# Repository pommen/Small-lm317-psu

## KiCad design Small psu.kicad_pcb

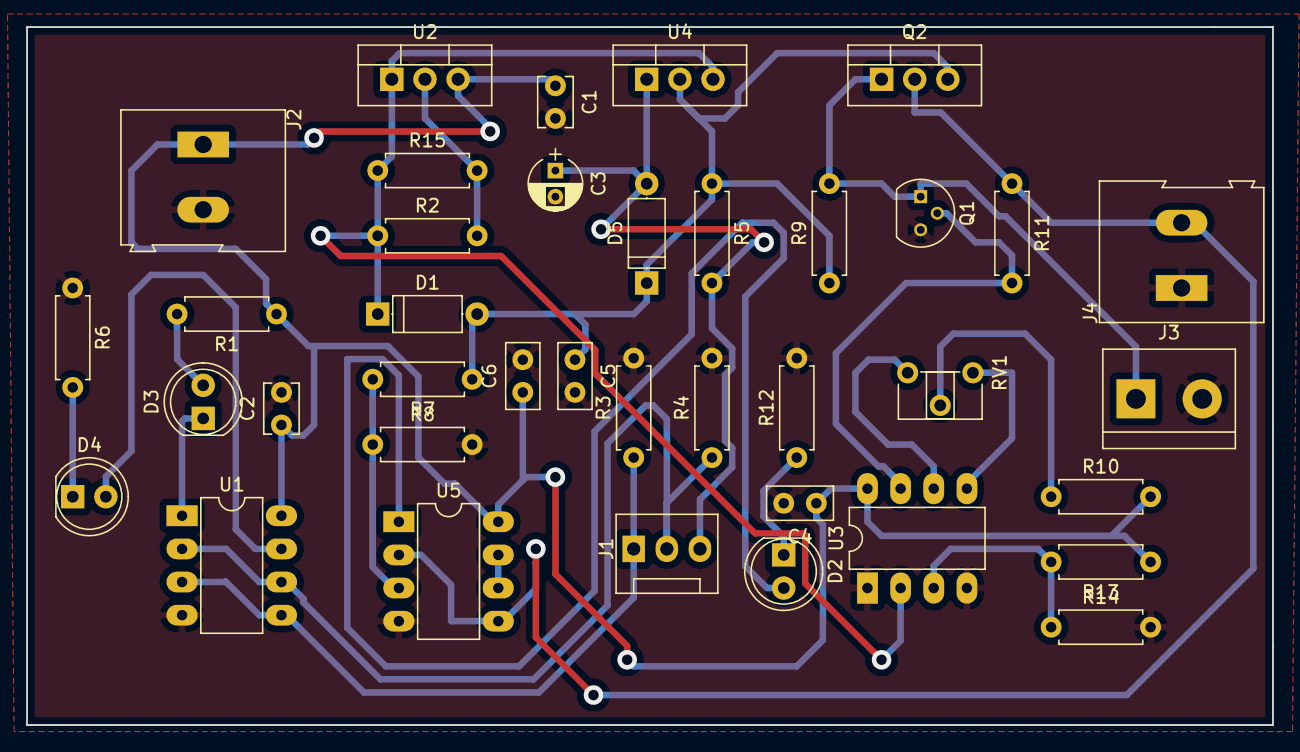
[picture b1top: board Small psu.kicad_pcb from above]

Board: 2 copper layers, 95.5 x 53.5 mm, 38 parts (0 on the bottom side), 23 nets.

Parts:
C1, C2: 0.1u; C_Disc_D3.8mm_W2.6mm_P2.50mm
C3: 10u; CP_Radial_D4.0mm_P2.00mm
C4, C6: 0.1u; C_Disc_D5.0mm_W2.5mm_P2.50mm
C5: 1u; C_Disc_D5.0mm_W2.5mm_P2.50mm
D1, D5: 1n4002; D_A-405_P7.62mm_Horizontal
D2: CC LED; LED_D5.0mm
D3: 5v LED; LED_D5.0mm
D4: 3v LED; LED_D5.0mm
J1: V select sw; Fan_Pin_Header_Straight_1x03
J2: VDC-in; AK300-2
J3: reset sw; bornier2
J4: V out; AK300-2
Q1: BC547; TO-92_Molded_Narrow
Q2: FQP27P06; TO-220_Vertical
R1, R3, R6: 1k6; R_Axial_DIN0207_L6.3mm_D2.5mm_P7.62mm_Horizontal
R2, R15: R; R_Axial_DIN0207_L6.3mm_D2.5mm_P7.62mm_Horizontal
R4: 3k; R_Axial_DIN0207_L6.3mm_D2.5mm_P7.62mm_Horizontal
R5, R14: 1k; R_Axial_DIN0207_L6.3mm_D2.5mm_P7.62mm_Horizontal
R7, R8, R12, R13: 4k7; R_Axial_DIN0207_L6.3mm_D2.5mm_P7.62mm_Horizontal
R9, R11: 100k; R_Axial_DIN0207_L6.3mm_D2.5mm_P7.62mm_Horizontal
R10: 5k6; R_Axial_DIN0207_L6.3mm_D2.5mm_P7.62mm_Horizontal
RV1: 5k; Potentiometer_Trimmer_ACP_CA6h_Vertical
U1, U5: LM358; DIP-8_W7.62mm_LongPads
U2, U4: LM317T; TO-220_Vertical
U3: LM311N; DIP-8_W7.62mm_LongPads

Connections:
3v3LED: J1.1, R3.1, U1.3, U1.5
5vLED: J1.2, R4.1, U1.2, U1.6
GND: C1.2, C2.2, C3.2, C4.2, C5.2, C6.2, J2.2, J3.2, J4.1, Q1.3, R3.2, R4.2, R6.1, R8.2, R12.2, R14.2, U1.4, U3.1, U3.4, U5.4
unnamed: C3.1, D5.2, J1.3, R5.2, U4.1
unnamed: C5.1, D1.2, D5.1, Q2.3, R5.1, R7.1, R9.1, U4.2
unnamed: D2.1, R12.1
unnamed: D2.2, U5.1
unnamed: D3.1, U1.1
unnamed: D3.2, R1.2
unnamed: D4.1, R6.2
unnamed: D4.2, U1.7
unnamed: J3.1, Q1.1, Q2.1, R9.2
unnamed: J4.2, Q2.2, R11.1, U5.2, U5.5
unnamed: Q1.2, R11.2, U3.7
unnamed: R7.2, R8.1, U5.3
unnamed: R10.1, RV1.2
unnamed: R13.2, R14.1, U3.3
unnamed: R2.2, R15.2, U2.2
unnamed: RV1.1, U3.5
unnamed: RV1.3, U3.6
unnamed: U5.6, U5.7
VCC: C1.1, C2.1, C4.1, C6.1, J2.1, R1.1, R10.2, R13.1, U1.8, U2.3, U3.8, U5.8
comp+: D1.1, R2.1, R15.1, U2.1, U3.2, U4.3
